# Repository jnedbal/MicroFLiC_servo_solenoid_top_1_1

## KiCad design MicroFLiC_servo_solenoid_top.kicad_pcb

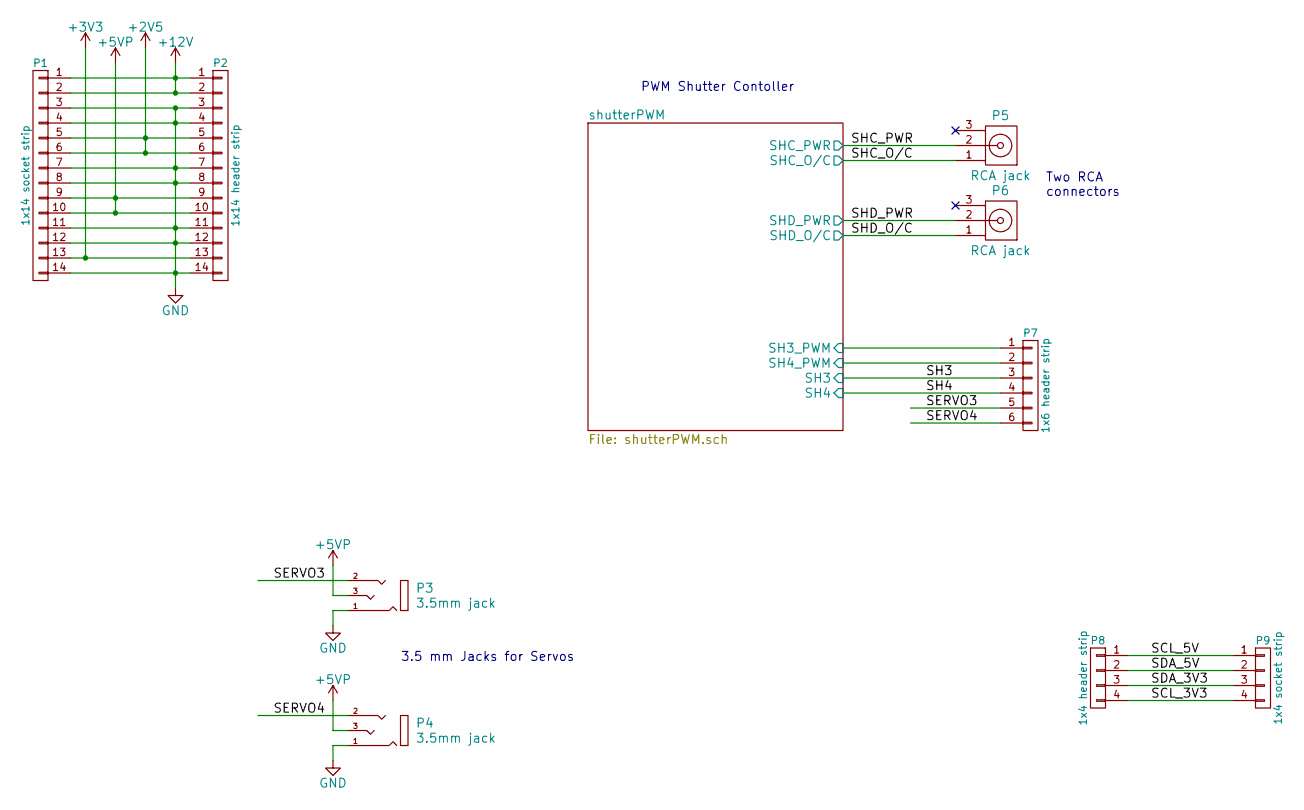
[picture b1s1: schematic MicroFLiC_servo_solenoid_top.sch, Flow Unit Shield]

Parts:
P1: 1x14 socket strip; ESQ-114-33-G-S; Part Number MC34735
P2: 1x14 header strip; Pin_Header_Straight_1x14; Part Number ESQ-114-33-G-S
P3, P4: 3.5mm jack; MJ4435-R; Part Number MJ4435-R
P5, P6: RCA jack; PSG01544; Part Number PSG01540
P7: 1x6 header strip; Pin_Header_Straight_1x06; Part Number ESQ-106-33-G-S
P8: 1x4 header strip; Pin_Header_Straight_1x04; Part Number M20-9990445
P9: 1x4 socket strip; ESQ-104-33-G-S; Part Number ESQ-104-33-G-S

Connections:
+2V5: P1.5, P1.6, P2.5, P2.6; also elsewhere on the board
+3V3: P1.13, P2.13
+5VP: P1.9, P1.10, P2.9, P2.10, P3.3, P4.3; also elsewhere on the board
+12V: P1.1, P1.2, P2.1, P2.2; also elsewhere on the board
/SCL_3V3: P8.4, P9.4
/SCL_5V: P8.1, P9.1
/SDA_3V3: P8.3, P9.3
/SDA_5V: P8.2, P9.2
/SERVO3: P3.2, P7.5
/SERVO4: P4.2, P7.6
/shutterPWM/SH3: P7.3; also elsewhere on the board
/shutterPWM/SH3_PWM: P7.1; also elsewhere on the board
/shutterPWM/SH4: P7.4; also elsewhere on the board
/shutterPWM/SH4_PWM: P7.2; also elsewhere on the board
/shutterPWM/SHC_O/C: P5.1; also elsewhere on the board
/shutterPWM/SHC_PWR: P5.2; also elsewhere on the board
/shutterPWM/SHD_O/C: P6.1; also elsewhere on the board
/shutterPWM/SHD_PWR: P6.2; also elsewhere on the board
GND: P1.3, P1.4, P1.7, P1.8, P1.11, P1.12, P1.14, P2.3, P2.4, P2.7, P2.8, P2.11, P2.12, P2.14, P3.1, P4.1; also elsewhere on the board

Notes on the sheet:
Two RCA connectors
PWM Shutter Contoller
3.5 mm Jacks for Servos

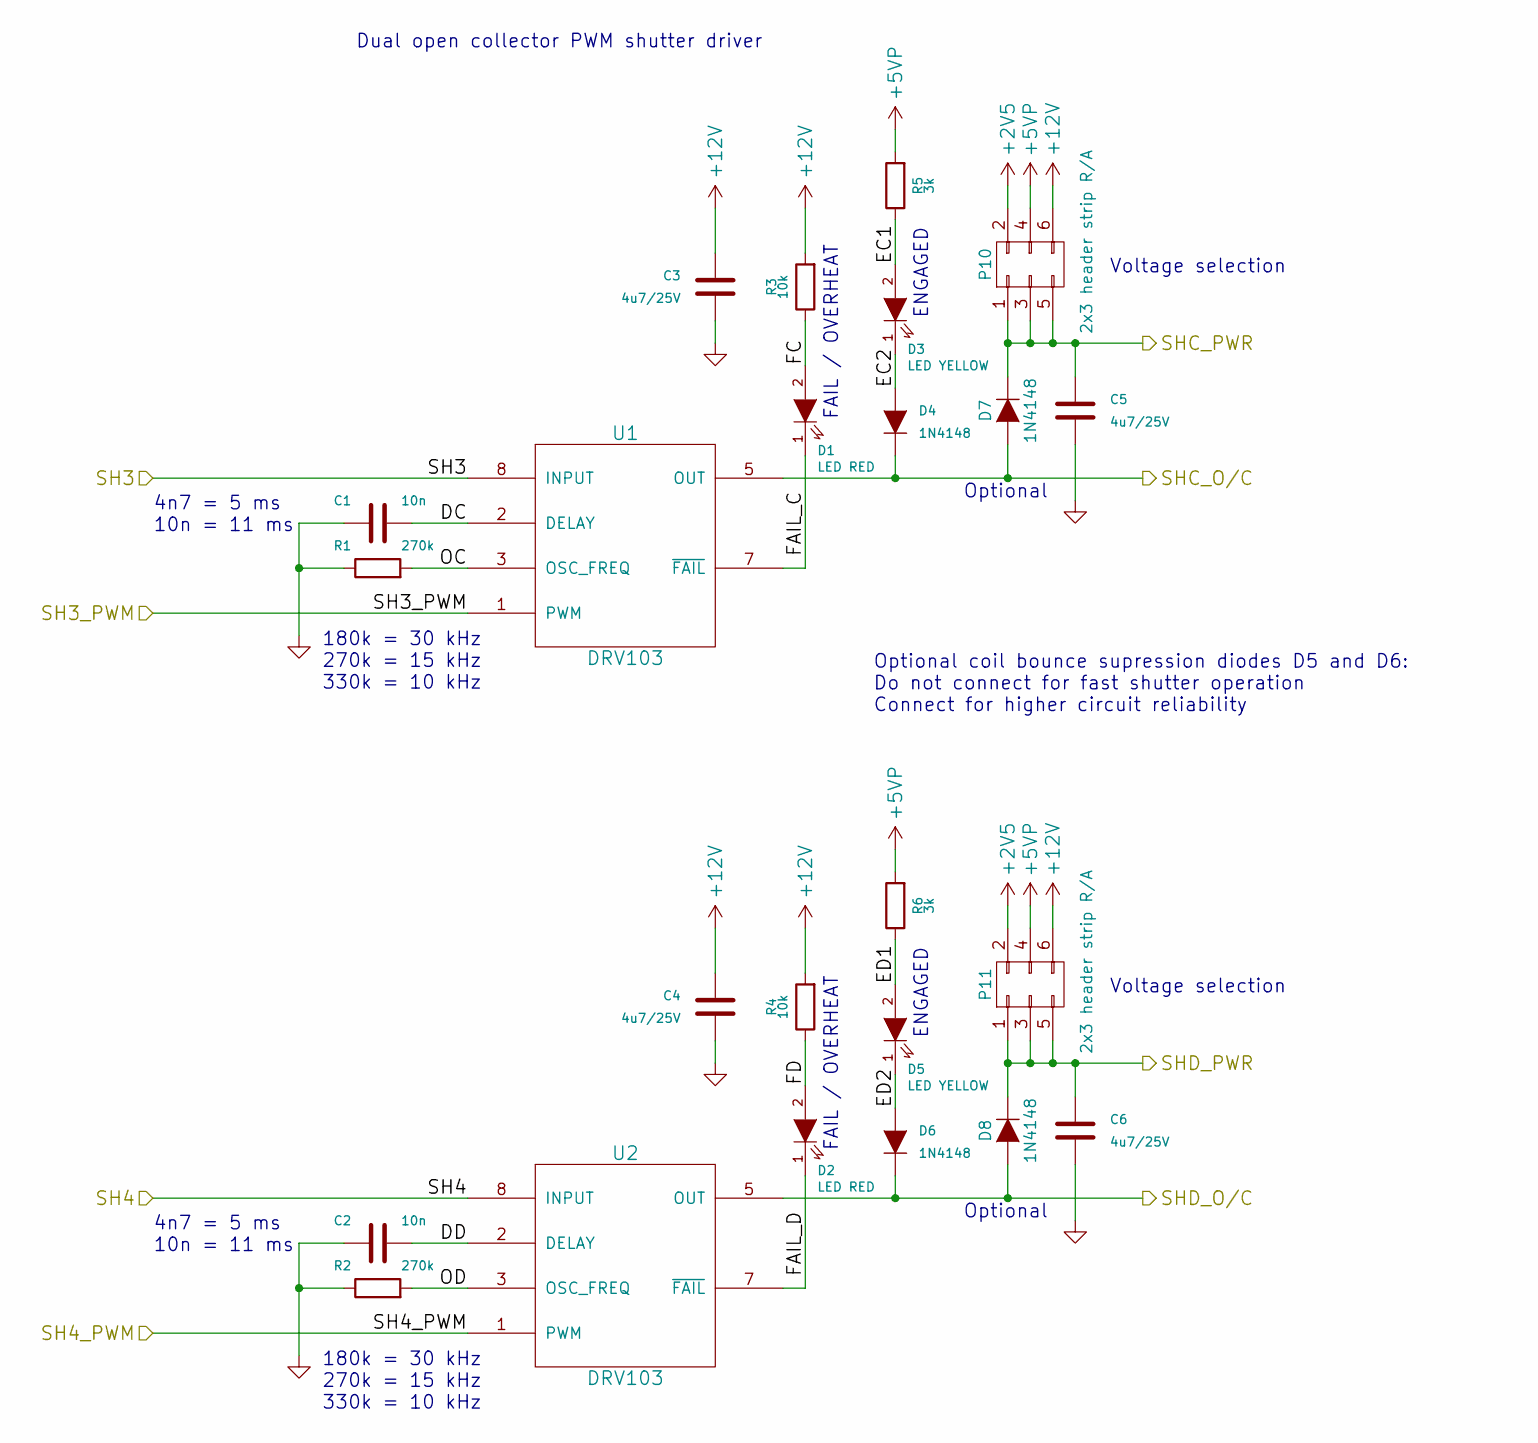
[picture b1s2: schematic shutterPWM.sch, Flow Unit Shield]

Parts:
C1, C2: 10n; C_0805; Part Number MCU0805R103KCT
C3, C4, C5, C6: 4u7/25V; C_0805; Part Number GRM21BR61E475MA12L
D1, D2: LED RED; LED-1206; Part Number HSMS-C150
D3, D5: LED YELLOW; LED-1206; Part Number HSMY-C150
D4, D6, D7, D8: 1N4148; SOD-323; Part Number 1N4148WS
P10, P11: 2x3 header strip R/A; Pin_Header_Angled_2x03; Part Number 2213R-06G
R1, R2: 270k; R_0805; Part Number MCSR08X2703FTL
R3, R4: 10k; R_0805; Part Number MCMR08X1002FTL
R5, R6: 3k; R_0805; Part Number MC01W080513K
U1, U2: DRV103; SOIC-8_3.9x4.9mm_Pitch1.27mm; Part Number DRV103UG4

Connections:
+2V5: P10.2, P11.2; also elsewhere on the board
+5VP: P10.4, P11.4, R5.2, R6.2; also elsewhere on the board
+12V: C3.2, C4.2, P10.6, P11.6, R3.2, R4.2, U1.6 (+12V), U2.6 (+12V); also elsewhere on the board
/shutterPWM/DC: C1.2, U1.2 (DELAY)
/shutterPWM/DD: C2.2, U2.2 (DELAY)
/shutterPWM/EC1: D3.2 (A), R5.1
/shutterPWM/EC2: D3.1 (K), D4.2 (A)
/shutterPWM/ED1: D5.2 (A), R6.1
/shutterPWM/ED2: D5.1 (K), D6.2 (A)
/shutterPWM/FAIL_C: D1.1 (K), U1.7 (~FAIL)
/shutterPWM/FAIL_D: D2.1 (K), U2.7 (~FAIL)
/shutterPWM/FC: D1.2 (A), R3.1
/shutterPWM/FD: D2.2 (A), R4.1
/shutterPWM/OC: R1.2, U1.3 (OSC_FREQ)
/shutterPWM/OD: R2.2, U2.3 (OSC_FREQ)
/shutterPWM/SH3: U1.8 (INPUT); also elsewhere on the board
/shutterPWM/SH3_PWM: U1.1 (PWM); also elsewhere on the board
/shutterPWM/SH4: U2.8 (INPUT); also elsewhere on the board
/shutterPWM/SH4_PWM: U2.1 (PWM); also elsewhere on the board
/shutterPWM/SHC_O/C: D4.1 (K), D7.2 (A), U1.5 (OUT); also elsewhere on the board
/shutterPWM/SHC_PWR: C5.2, D7.1 (K), P10.1, P10.3, P10.5; also elsewhere on the board
/shutterPWM/SHD_O/C: D6.1 (K), D8.2 (A), U2.5 (OUT); also elsewhere on the board
/shutterPWM/SHD_PWR: C6.2, D8.1 (K), P11.1, P11.3, P11.5; also elsewhere on the board
GND: C1.1, C2.1, C3.1, C4.1, C5.1, C6.1, R1.1, R2.1, U1.4 (GND), U2.4 (GND); also elsewhere on the board

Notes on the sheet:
Dual open collector PWM shutter driver
Optional coil bounce supression diodes D5 and D6: Do not connect for fast shutter operation Connect for higher circuit reliability
180k = 30 kHz 270k = 15 kHz 330k = 10 kHz
4n7 = 5 ms 10n = 11 ms
FAIL / OVERHEAT
ENGAGED
Voltage selection
Optional

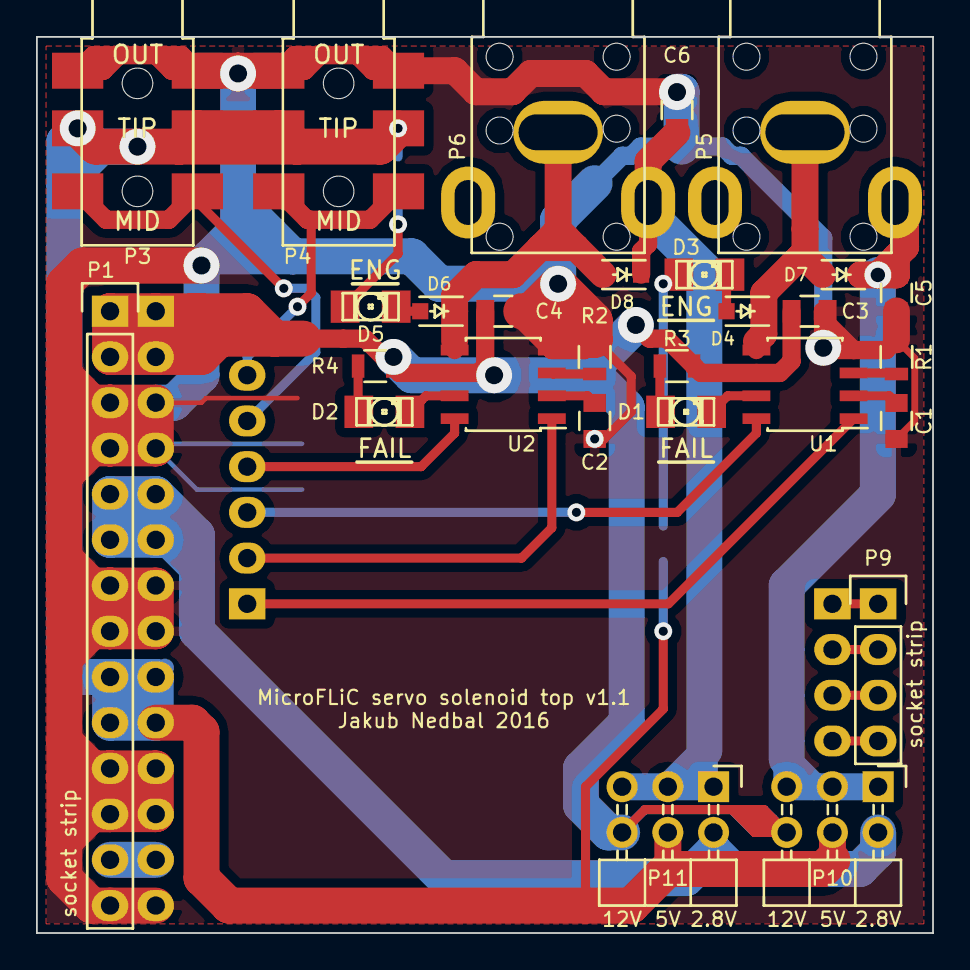
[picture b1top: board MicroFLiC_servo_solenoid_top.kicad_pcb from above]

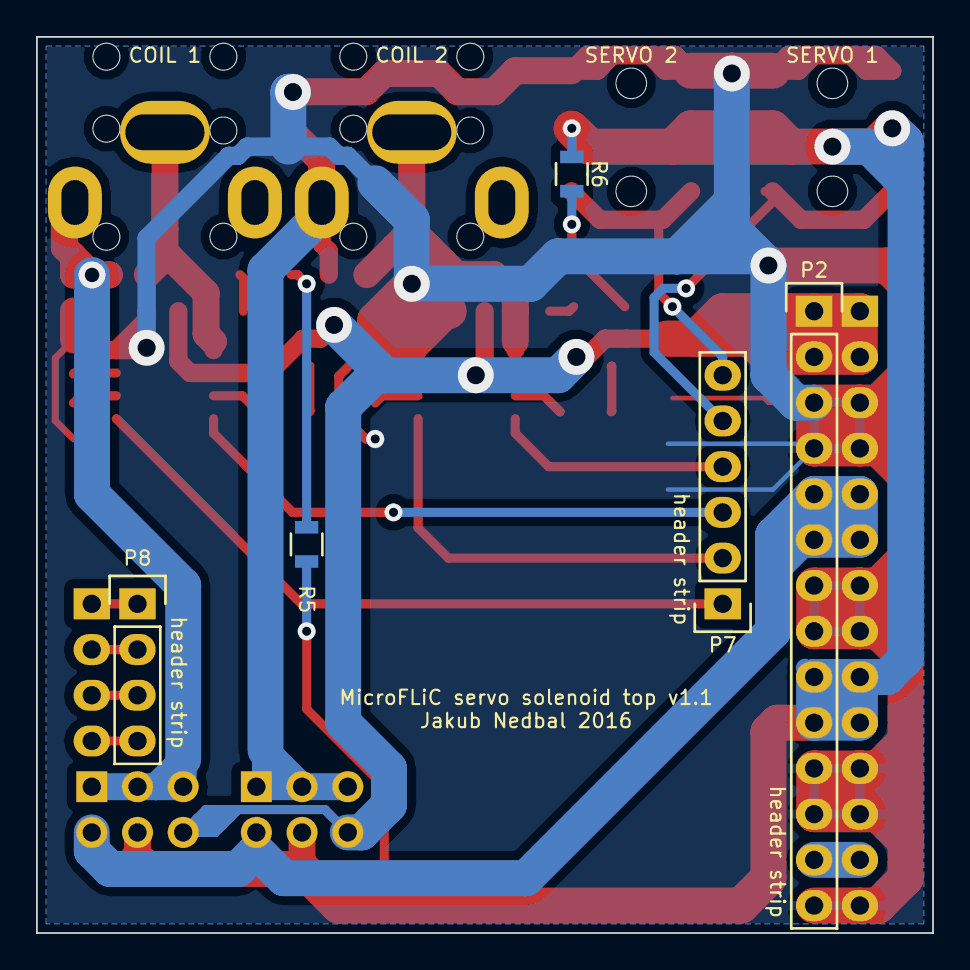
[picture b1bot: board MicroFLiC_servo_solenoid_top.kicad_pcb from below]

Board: 2 copper layers, 49.8 x 49.8 mm, 33 parts (5 on the bottom side), 31 nets.

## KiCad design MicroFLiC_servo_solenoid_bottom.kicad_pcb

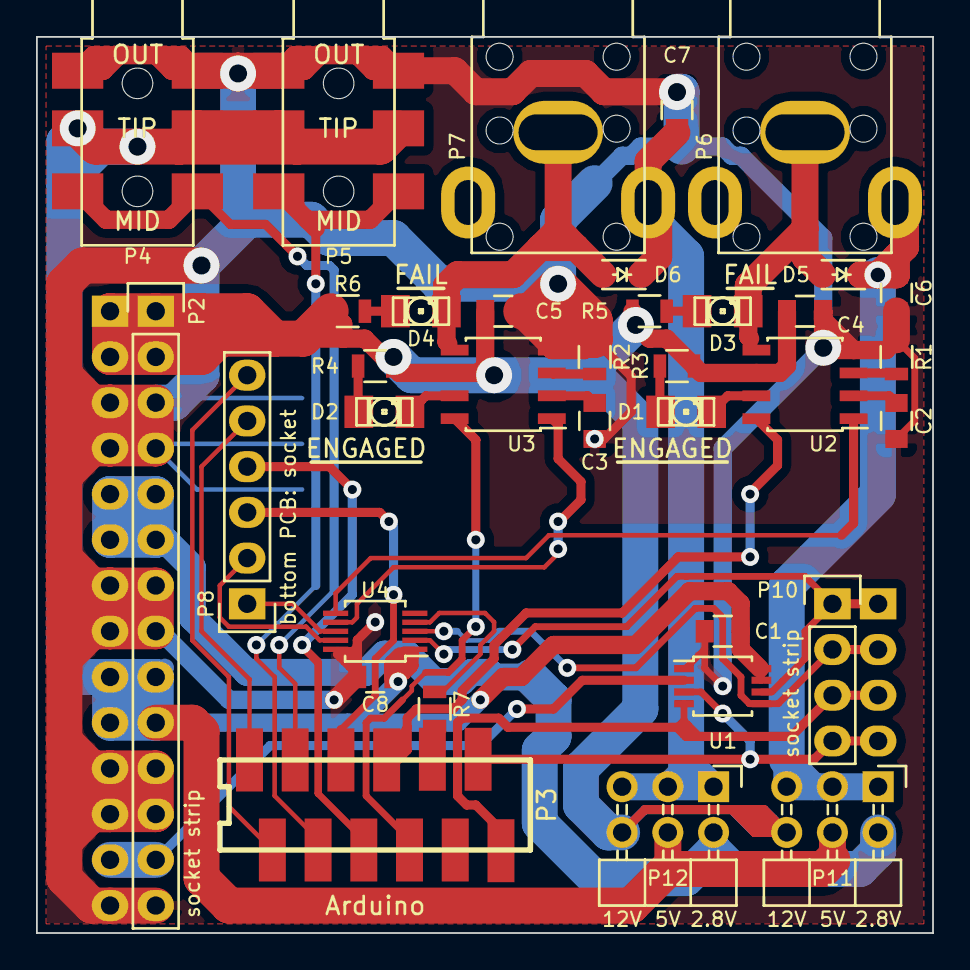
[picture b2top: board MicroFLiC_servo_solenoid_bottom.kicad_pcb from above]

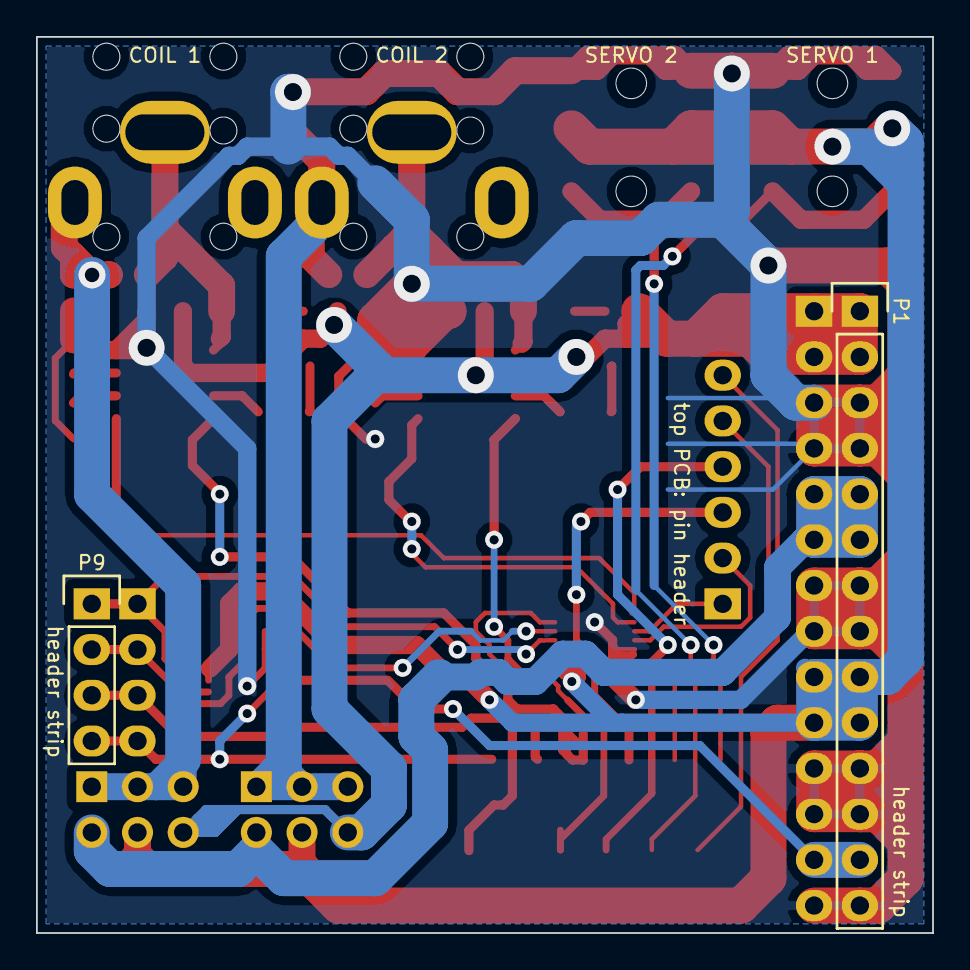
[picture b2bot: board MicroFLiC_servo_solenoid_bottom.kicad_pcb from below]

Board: 2 copper layers, 49.8 x 49.8 mm, 37 parts (2 on the bottom side), 37 nets.

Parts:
C1, C8: 100n; C_0805
C2, C3: 10n; C_0805
C4, C5, C6, C7: 4u7/25V; C_0805
D1, D2: LED RED; LED-1206
D3, D4: LED YELLOW; LED-1206
D5, D6: 1N4148; SOD-323
P1: 1x14 header strip; Pin_Header_Straight_1x14
P2: 1x14 socket strip; ESQ-114-33-G-S
P3: 12-way Micro-MaTch; 1-188275-2
P4, P5: Jack_3.5mm_3pin; MJ4435-R
P6, P7: RCA_3; PSG01544
P8: 1x6 socket strip; ESQ-106-33-G-S
P9: 1x4 header strip; Pin_Header_Straight_1x04
P10: 1x4 socket strip; ESQ-104-33-G-S
P11, P12: 2x3 header strip R/A; Pin_Header_Angled_2x03
R1, R2: 270k; R_0805
R3, R4, R5, R6: 10k; R_0805
R7: 0R; R_0805
U1: PCA9306DP; TSSOP-8_3x3mm_Pitch0.65mm
U2, U3: DRV103; SOIC-8_3.9x4.9mm_Pitch1.27mm
U4: MCP4728; MSOP-10_3x3mm_Pitch0.5mm

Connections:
+2V5: P1.5, P1.6, P2.5, P2.6, P11.2, P12.2
+3V3: P1.13, P2.13, U1.2
+5VP: C1.1, C8.2, P1.9, P1.10, P2.9, P2.10, P4.3, P5.3, P11.4, P12.4, U1.7, U1.8, U4.1
+12V: C4.2, C5.2, P1.1, P1.2, P2.1, P2.2, P11.6, P12.6, R3.2, R4.2, R5.2, R6.2, U2.6, U3.6
/I2C/SCL_3V3: P3.11, P9.4, P10.4, U1.3
/I2C/SCL_5V: P9.1, P10.1, U1.6, U4.2
/I2C/SDA_3V3: P3.12, P9.3, P10.3, U1.4
/I2C/SDA_5V: P9.2, P10.2, U1.5, U4.3
/SERVO1: P3.3, P4.2
/SERVO2: P3.4, P5.2
/SERVO3: P3.1, P8.5
/SERVO4: P3.2, P8.6
/SH3: P3.5, P8.3
/SH4: P3.6, P8.4
/shutterPWM/DA: C2.2, U2.2
/shutterPWM/DB: C3.2, U3.2
/shutterPWM/EA: D1.2, R3.1
/shutterPWM/EB: D2.2, R4.1
/shutterPWM/ENG_A: D1.1, U2.7
/shutterPWM/ENG_B: D2.1, U3.7
/shutterPWM/FA: D3.2, R5.1
/shutterPWM/FB: D4.2, R6.1
/shutterPWM/OA: R1.2, U2.3
/shutterPWM/OB: R2.2, U3.3
/shutterPWM/SH1: P3.7, U2.8
/shutterPWM/SH1_PWM: U2.1, U4.6
/shutterPWM/SH2: P3.8, U3.8
/shutterPWM/SH2_PWM: U3.1, U4.7
/shutterPWM/SH3_PWM: P8.1, U4.8
/shutterPWM/SH4_PWM: P8.2, U4.9
/shutterPWM/SHA_O/C: D3.1, D5.2, P6.1, U2.5
/shutterPWM/SHA_PWR: C6.2, D5.1, P6.2, P11.1, P11.3, P11.5
/shutterPWM/SHB_O/C: D4.1, D6.2, P7.1, U3.5
/shutterPWM/SHB_PWR: C7.2, D6.1, P7.2, P12.1, P12.3, P12.5
/shutterPWM/SH_~LDAC: P3.9, R7.1
GND: C1.2, C2.1, C3.1, C4.1, C5.1, C6.1, C7.1, C8.1, P1.3, P1.4, P1.7, P1.8, P1.11, P1.12, P1.14, P2.3, P2.4, P2.7, P2.8, P2.11, P2.12, P2.14, P4.1, P5.1, R1.1, R2.1, U1.1, U2.4, U3.4, U4.10
unnamed: R7.2, U4.4

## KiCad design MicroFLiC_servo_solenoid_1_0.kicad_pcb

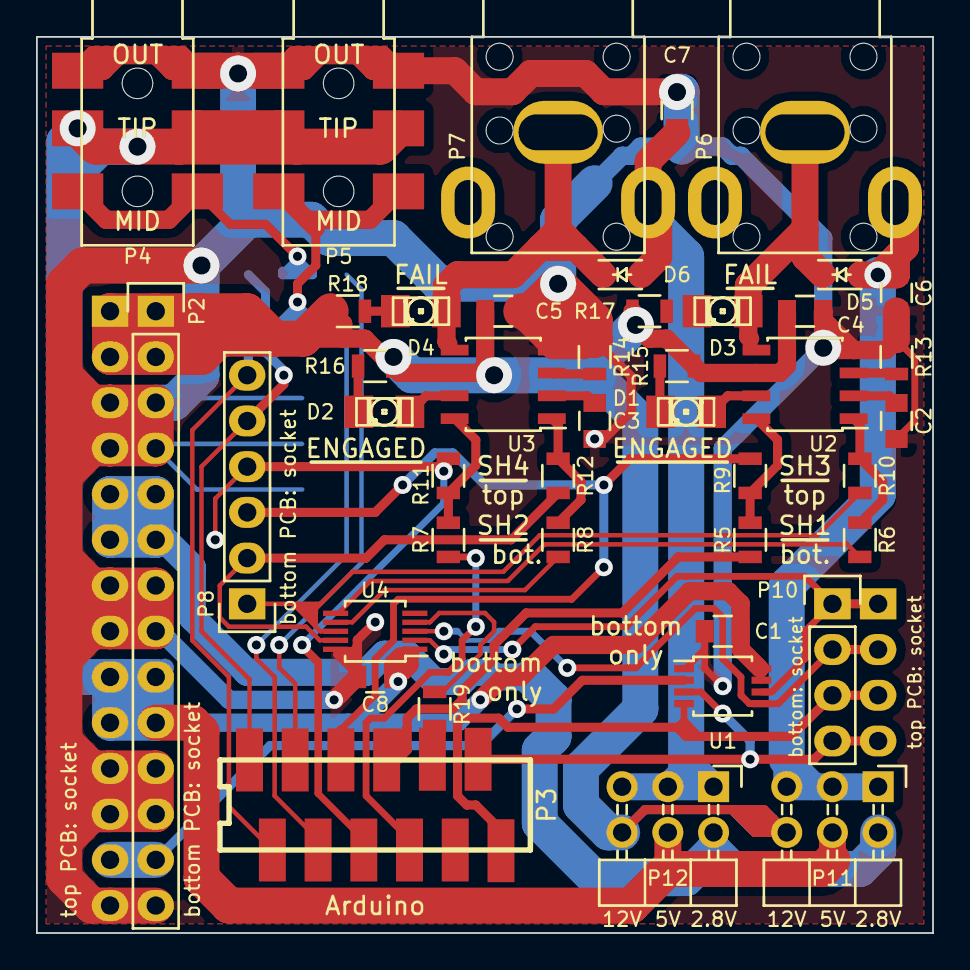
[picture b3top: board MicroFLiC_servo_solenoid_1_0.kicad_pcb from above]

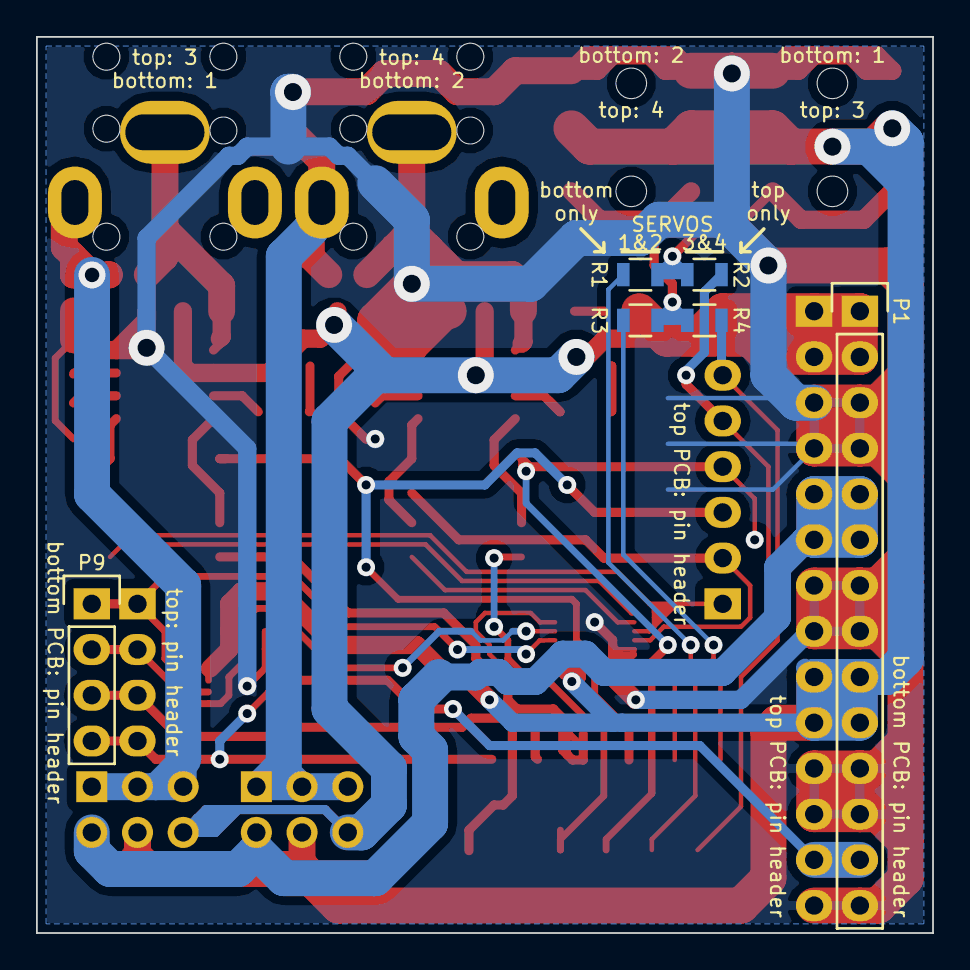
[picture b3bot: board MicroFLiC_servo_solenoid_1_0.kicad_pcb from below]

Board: 2 copper layers, 49.8 x 49.8 mm, 49 parts (6 on the bottom side), 43 nets.

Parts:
C1, C8: 100n; C_0805
C2, C3: 10n; C_0805
C4, C5: 4u7/25V; C_0805
C6, C7: 10u/25V; C_0805
D1, D2: YELLOW; LED-1206
D3, D4: RED; LED-1206
D5, D6: PMEG2020; SOD-323
P1: Header_1x14; Pin_Header_Straight_1x14
P2: Socket_1x14; ESQ-114-33-G-S
P3: 12-way Micro-MaTch; 1-188275-2
P4, P5: Jack_3.5mm_3pin; MJ4435-R
P6, P7: RCA_3; PSG01544
P8: Socket_1x6; ESQ-106-33-G-S
P9: Header_1x4; Pin_Header_Straight_1x04
P10: Socket_1x4; ESQ-104-33-G-S
P11, P12: Header_R/A_2x3; Pin_Header_Angled_2x03
R1, R2, R3, R4, R5, R6, R7, R8, R9, R10, R11, R12, R19: 0R; R_0805
R13, R14: 270k; R_0805
R15, R16, R17, R18: 10k; R_0805
U1: PCA9306; TSSOP-8_3x3mm_Pitch0.65mm
U2, U3: DRV103; SOIC-8_3.9x4.9mm_Pitch1.27mm
U4: MCP4728; MSOP-10_3x3mm_Pitch0.5mm

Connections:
+2V5: P1.5, P1.6, P2.5, P2.6, P11.2, P12.2
+3V3: P1.13, P2.13, U1.2
+5VP: C1.1, C8.2, P1.9, P1.10, P2.9, P2.10, P4.3, P5.3, P11.4, P12.4, U1.7, U1.8, U4.1
+12V: C4.2, C5.2, P1.1, P1.2, P2.1, P2.2, P11.6, P12.6, R15.2, R16.2, R17.2, R18.2, U2.6, U3.6
/I2C/SCL_3V3: P3.11, P9.4, P10.4, U1.3
/I2C/SCL_5V: P9.1, P10.1, U1.6, U4.2
/I2C/SDA_3V3: P3.12, P9.3, P10.3, U1.4
/I2C/SDA_5V: P9.2, P10.2, U1.5, U4.3
/SERVO1: P3.3, R1.1
/SERVO2: P3.4, R3.1
/SERVO3: P3.1, P8.5, R2.1
/SERVO4: P3.2, P8.6, R4.1
/SERVOA: P4.2, R1.2, R2.2
/SERVOB: P5.2, R3.2, R4.2
/shutterPWM/DA: C2.2, U2.2
/shutterPWM/DB: C3.2, U3.2
/shutterPWM/EA: D1.1, R15.1
/shutterPWM/EB: D2.1, R16.1
/shutterPWM/ENG_A: D1.2, U2.7
/shutterPWM/ENG_B: D2.2, U3.7
/shutterPWM/FA: D3.1, R17.1
/shutterPWM/FB: D4.1, R18.1
/shutterPWM/OA: R13.2, U2.3
/shutterPWM/OB: R14.2, U3.3
/shutterPWM/SH1: P3.7, R5.1
/shutterPWM/SH1_PWM: R6.1, U4.6
/shutterPWM/SH2: P3.8, R7.1
/shutterPWM/SH2_PWM: R8.1, U4.7
/shutterPWM/SH3: P3.5, P8.3, R9.2
/shutterPWM/SH3_PWM: P8.1, R10.2, U4.8
/shutterPWM/SH4: P3.6, P8.4, R11.2
/shutterPWM/SH4_PWM: P8.2, R12.2, U4.9
/shutterPWM/SHA_IN: R5.2, R9.1, U2.8
/shutterPWM/SHA_O/C: D3.2, D5.1, P6.1, U2.5
/shutterPWM/SHA_PWM: R6.2, R10.1, U2.1
/shutterPWM/SHA_PWR: C6.2, D5.2, P6.2, P11.1, P11.3, P11.5
/shutterPWM/SHB_IN: R7.2, R11.1, U3.8
/shutterPWM/SHB_O/C: D4.2, D6.1, P7.1, U3.5
/shutterPWM/SHB_PWM: R8.2, R12.1, U3.1
/shutterPWM/SHB_PWR: C7.2, D6.2, P7.2, P12.1, P12.3, P12.5
/shutterPWM/SH_~LDAC: P3.9, R19.1
GND: C1.2, C2.1, C3.1, C4.1, C5.1, C6.1, C7.1, C8.1, P1.3, P1.4, P1.7, P1.8, P1.11, P1.12, P1.14, P2.3, P2.4, P2.7, P2.8, P2.11, P2.12, P2.14, P4.1, P5.1, R13.1, R14.1, U1.1, U2.4, U3.4, U4.10
unnamed: R19.2, U4.4

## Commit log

2016-01-06 Final production board v1.0
2016-02-19 Added component descriptions
2016-02-28 Renamed solenoid to v1.1, added part descriptions
2016-02-29 Deleted redundant resistors and labels from PCB
2016-02-29 Fixed PCB routing
2016-02-29 Created v1.1, got rid of all redundant parts for separate top and bottom boards
2016-02-29 Removed I2C.sch
2016-03-02 Added better de-bouncing diode description
2016-03-18 Changed ENGAGED LED anode to +5V, changed SOD-323 packages, tidied up layout
